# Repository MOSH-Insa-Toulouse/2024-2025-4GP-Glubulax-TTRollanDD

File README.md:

# 2024-2025 : Projet de capteur graphène low-tech – Sombret Yanis, Rolland Tristan

## SOMMAIRE

- [2024-2025 : Projet de capteur graphène low-tech – Sombret Yanis, Rolland Tristan](#2024-2025--projet-de-capteur-graphène-low-tech--sombret-yanis-rolland-tristan)
  - [SOMMAIRE](#sommaire)
  - [Présentation du projet](#présentation-du-projet)
  - [Livrables](#livrables)
  - [Matériel nécessaire](#matériel-nécessaire)
  - [Simulation électronique du capteur sous LTSpice](#simulation-électronique-du-capteur-sous-ltspice)
  - [Design du PCB sous KiCad et réalisation de la Shield](#design-du-pcb-sous-kicad-et-réalisation-de-la-shield)
  - [Code Arduino et applications](#code-arduino-et-applications)
  - [Test et résultats](#test-et-résultats)
  - [Datasheet](#datasheet)
  - [Conclusions et analyse critique du projet](#conclusions-et-analyse-critique-du-projet)
  - [Contacts](#contacts)

## Présentation du projet

&nbsp;&nbsp;&nbsp;&nbsp;&nbsp;&nbsp;Dans le cadre de l’UF «Du capteur au banc de test», nous avons eu pour projet de designer et produire un système de mesure de déformation d’une jauge de contrainte low-tech, un morceau de papier sur lequel est dessiné une piste au crayon à papier. Cette technologie bas coût de jauge de contrainte provient des travaux de Cheng-Wei Lin, Zhibo Zhao, Jaemyung Kim et Jiaxing Huang, chercheurs du département des sciences de l’ingénierie et des matériaux de l’université Northwestern à Evanston, USA. En effet, les traces de crayons laissées sur le papier jouent le rôle de fines couches de graphène conductrices. 

&nbsp;&nbsp;&nbsp;&nbsp;&nbsp;&nbsp;En fonction de la contrainte appliquée à notre jauge, l’écartement des particules de graphène se voit modifié, altérant les propriétés conductrices de notre couche de graphène. Grossièrement, effectuer une flexion sur notre capteur revient à écarter les agglomérats de graphène diminuant la conductivité, effectuer une compression revient à produire l’effet inverse en rapprochant les agglomérats de graphène. 

&nbsp;&nbsp;&nbsp;&nbsp;&nbsp;&nbsp;Par mesure de tension en sortie d’amplificateur, il est possible de remonter à la valeur de la résistance du capteur et la mettre en regard de la déformation. Enfin, la quantité de graphène dépend du type de crayon employé influant aussi la conductivité de la couche obtenue. 

&nbsp;&nbsp;&nbsp;&nbsp;&nbsp;&nbsp;Ainsi, en plus de l’intérêt pédagogique de ce projet de conception qui nous a permis d’intervenir sur toute la chaîne d’acquisition, nous avons eu l’occasion, et pour mission, de faire une étude qualitative du banc de test et déterminer ainsi si le capteur pouvait faire l’objet d’une commercialisation, et si oui, avec quel type de crayon à papier. 

&nbsp;&nbsp;&nbsp;&nbsp;&nbsp;&nbsp;Dans le cadre de la réalisation et de la caractérisation de ce dispositif de mesure low-tech, il nous a fallu suivre différentes étapes allant de la simulation électronique à la rédaction de sa datasheet en passant par l’impression de notre Shield PCB sur lequel nous avons fait nos soudures.

Dans ce README, nous faisons état de tout ce qui a été fait dans le cadre de ce projet.

## Livrables

Plusieurs livrables sont attendus :

- **Un Shield PCB connecté à une carte Arduino UNO** avec différents composants : un capteur graphite, un amplificateur transimpédance, un module Bluetooth, un écran OLED, un flexsensor commercial, un potentiomètre digital, un encodeur rotatoire ;
- **Le code Arduino lié** permettant de contrôler les différents composants intégrés et de faire fonctionner les différentes fonctionnalités de notre assemblage (mesures de contraintes, échanges Bluetooth et OLED, potentiomètre digital et boutons) ;
- **Une application Android** (sous MIT App Inventor) interfaçant le PCB et le code Arduino correspondant, aidant à la prise des mesures ;
- **La datasheet du capteur** reprenant toutes les caractéristiques notre capteur low-tech.

## Matériel nécessaire

Afin de mener notre projet à son aboutissement, nous avons eu besoin de :

*Pour le montage de l'amplificateur transimpédance : *

- Résistances fixes : 1 kΩ x1, 10 kΩ x1, 100 kΩ x2 ; une résistance variable (le potentiomètre digital), afin de pouvoir régler le gain de notre amplificateur ;
- Une résistance variable (Potentiomètre digital MCP41050 et son support), afin de pouvoir régler le gain de notre montage amplificateur ;
- Amplificateur opérationnel LTC1050 et son support ;
- Capacités : 100 nF x3, 1 μF x1.

*Pour le reste de notre Shield :*

- Arduino Uno et son câble d’alimentation, notre carte d’acquisition ;
- Résistance : une de 33kΩ similaire à la résistance au repos du flexsensor afin de réaliser un pont diviseur de tension ;
- Module Bluetooth HC05 ;
- Ecran OLED de dimension 128*64 ;
- Flexsensor ;
- Encodeur rotatoire ;
- Capteur graphite et 2 pinces crocodiles ;

## Simulation électronique du capteur sous LTSpice

&nbsp;&nbsp;&nbsp;&nbsp;&nbsp;&nbsp;Notre capteur passif en graphène possède une très grande résistance, de l’ordre du mégaohm. Ainsi, une fois alimenté par la carte Arduino en 5V à ces bornes, le courant est très faible. Or, il est notre signal d’intérêt pour remonter à la valeur de la résistance de notre capteur. Ainsi, il est nécessaire de mettre en place un amplificateur transimpédance afin d’amplifier le signal, le convertir en tension, et enfin de diminuer les bruits en entrés qui pourrait parasiter notre signal trop faible. Pour se faire, nous avons d’abord modélisé l’amplificateur sous LTspice afin d’optimiser au mieux sa conception pour notre application.

***Description du montage amplificateur transimpédance***

Nous avons testé ce [montage](https://github.com/MOSH-Insa-Toulouse/2024-2025-4GP-Glubulax-TTRollanDD/blob/5d5dbacb22e8d05c2202cd88c66fef8cc0433a9e/LTspice/Ampli_transimp%C3%A9dance/Ampli_transimp%C3%A9dance.asc) sur le logiciel LTspice :

Via ce montage, on a le rapport :

Vcc/Vadc=(Rcapteur+R1+R5)/(1+R3/R2)R1

On peut donc remonter à la valeur de la résistance du capteur :

Rcapteur=(1+R3/R2)R1*Vcc/Vadc-R1-R5

&nbsp;&nbsp;&nbsp;&nbsp;&nbsp;&nbsp;Aussi, nous remplacerons R2 sur notre PCB finale par un potentiomètre digital afin de pouvoir régler pendant nos mesures le gain du montage dans le cas de saturation par exemple.

&nbsp;&nbsp;&nbsp;&nbsp;&nbsp;&nbsp;Le choix de l’amplificateur opérationnel de notre circuit ici est crucial. Celui-ci doit être capable d'accepter en entrée un très faible courant et posséder un offset de tension très faible afin de ne pas fausser les valeurs de tension en sortie du montage. Contraintes vérifiées par simulation. Après plusieurs essaies guidés, le choix le plus pertinent était l’AOP LTC 1050.

&nbsp;&nbsp;&nbsp;&nbsp;&nbsp;&nbsp;Place maintenant à la réduction du bruit. Pour obtenir un signal le plus pur et ce, de manière efficace, nous avons dimensionné les 3 filtres de ce montage amplificateur transimpédance via nos simulations. Chaque filtre ayant un rôle bien précis : 

- à l'entrée, un filtre 1 passe-bas passif (R5,R1,C1) avec une fréquence de coupure de 16 Hz permettant de filtrer les bruits sur le signal en entrée fournis par nos capteurs. Donc tout type de perturbations en courant qu’il pourrait avoir lieu avant amplification, qui serait amplifié dans le cas contraire avec notre signal, le noyant.

- un deuxième filtre 2 passe-bas avec une fréquence de coupure de 1.6 Hz (R3,C4) couplé à l'AOP permettant de filtrer la composante du bruit à 50 Hz provenant du réseau électrique. Ici, la simulation nous a permis de fixer la valeur de C4. Une valeur trop élevée permet de diminuer grandement le bruit à 50 Hz mais diminue fortement le temps de réponse de notre circuit amplificateur. Ainsi, après simulation, fixer C4 à 1μF représente le meilleur compromis. 

- à la sortie de l'amplificateur, le filtre 3 (R6,C2) avec une fréquence de coupure de 1.6 kHz permettant de filtrer le bruit provenant du fonctionnement du LTC1050 (bruits des alimentation, de l'horloge, etc...).

&nbsp;&nbsp;&nbsp;&nbsp;&nbsp;&nbsp;Enfin, la résistance R5 en entrée, en plus de former avec la capacité C1 un filtre éliminant les bruits en tension, protège l'AOP contre les décharges électrostatiques et permet d’obtenir la conversion du signal en tension. La résistance R1 sert de résistance de shunt entre la source de courant et la masse.

***Résultats simulations***

&nbsp;&nbsp;&nbsp;&nbsp;&nbsp;&nbsp;Comme énoncé précédemment, la simulation nous a permis de vérifier la théorie et d’optimiser certains filtres afin d’obtenir les meilleurs rapports signal/temps de réponse. Voici les résultats des simulations.

&nbsp;&nbsp;&nbsp;&nbsp;&nbsp;&nbsp;On observe bien ci-dessus l’amplification du signal. L'Arduino pourra donc l'interpréter. De plus, on vérifie que plus C4 est élevée, meilleur le signal est mais plus le temps de réponse est long.

&nbsp;&nbsp;&nbsp;&nbsp;&nbsp;&nbsp;Ci-dessous les résultats de nos simulations à courant alternatifs afin de vérifier et optimiser le rôle de chacun des filtres. Le bruit est atténué d’environ 72dB à 50Hz. Le montage est performant.

## Design du PCB sous KiCad et réalisation de la Shield

***Modélisation sous KiCad***

&nbsp;&nbsp;&nbsp;&nbsp;&nbsp;&nbsp;Une fois les étapes de vérification faites, nous pouvions commencer le design et la conception de notre banc de test. Pour se faire nous avons utilisé le logiciel de modélisation KiCad 9.0, qui permet de modéliser tous les composants dont nous avions besoin sur une Shield de taille identique à la plaquette Arduino qui servira de carte d’acquisition. De là, nous pouvions modéliser nos différents composant et faire la connectique, étape très importante étant donné la petitesse de notre PCB en regard des composants qu’elle accueillerait. Afin de réaliser nos mesures avec le plus de pertinence et de confort, nous avons eu recourt à:

- un flexsensor commercial d’une résistance au repos de 33kΩ, afin de pouvoir comparer nos mesures avec celle des capteurs graphites.

- un module bluetooth HC-05 permettant d’envoyer les données mesurées sur notre téléphone via une application Android codé par nos soins sur MIT APP Inventor.

- un écran OLED permettant d’afficher un menu sur lequel nous pouvons régler la valeur de la résistance du potentiomètre digital ainsi qu’observer la valeur des résistances du flexsensor et des capteurs graphènes. 

&nbsp;&nbsp;&nbsp;&nbsp;&nbsp;&nbsp;Pour la modélisation, nous avons commencé par faire la schématique. Cette dernière permet de visualiser et de faire tous les branchements nécessaires au bon fonctionnement de notre banc de test. Fi de fils de connections, c’est le fonctionnement qui importe. Nous avons dû créer nous même certains symboles non présents dans les bibliothèques déjà existantes. Notre seule contrainte ici était de connecter les bons éléments aux pins d’intérêts de l’arduino. En effet, certain composant nécessitait d’être connecté à des pins PWM de l’arduino pour cadencer l’information via une clock. C’est le cas pour le module HC-05 en écriture au moins et l’encodeur digital. Voici donc notre proposition :

&nbsp;&nbsp;&nbsp;&nbsp;&nbsp;&nbsp;Par la suite, nous avons créé les empreintes de chacun des composants afin de modéliser notre Shield PCB. C’est à cette étape que nous prenions en compte les pistes de cuivres et l’agencement des composants pour que tout rentre sur l’espace imposé et que tout soit connecté selon la schématique que nous avions produit précédemment. Aussi, il nous a fallu prêter grande attention aux masses flottantes et aux piscines. Les masses flottantes pouvaient générer des disfonctionnements sur notre banc. Quant aux piscines, de larges zones sans cuivre, elles posaient un problème de gaspillage, les pistes après modélisation se faisant par enlèvement de matière.  

&nbsp;&nbsp;&nbsp;&nbsp;&nbsp;&nbsp;Il nous a également fallu prendre en compte les dimensions de chaque composant pour éviter qu’ils ne se chevauchent au moment de la réalisation :

&nbsp;&nbsp;&nbsp;&nbsp;&nbsp;&nbsp;Les fichiers KiCad sont disponibles dans le dossier [KiCad arduino uno](https://github.com/MOSH-Insa-Toulouse/2024-2025-4GP-Glubulax-TTRollanDD/tree/5d5dbacb22e8d05c2202cd88c66fef8cc0433a9e/Kicad%20arduino%20uno/Capteur_graphite).

***Réalisation de la Shield***

&nbsp;&nbsp;&nbsp;&nbsp;&nbsp;&nbsp;Modélisation terminée, nous avons pu passer à la réalisation physique de notre Shield. Voici les étapes de fabrication réalisées :

Étape 0 (importante !) : vérification du PCB sous KiCad ;
Étape 1 : édition du masque de gravure de notre PCB sous KiCad ;
Étape 2 : insolation UV d'une plaquette d'époxy recouverte d'une couche de cuivre et de résine photosensible ;
Étape 3 : immersion de la plaquette dans un révélateur afin d'éliminer la résine non-insolée ;
Étape 4 : immersion de la plaquette dans du perchlorure de fer pour graver les pistes ;
Étape 5 : nettoyage de la plaquette avec de l'acétone pour retirer la résine restante.

&nbsp;&nbsp;&nbsp;&nbsp;&nbsp;&nbsp;Toutes ces étapes de fabrication ont été réalisées par Cathy Crouzet. Nous avons ensuite pu réaliser le perçage de notre plaquette et y souder nos divers composants selon le schéma du PCB obtenu sur KiCad.

Voici le résultat après soudure de notre PCB :

## Code Arduino et applications

***Arduino***

&nbsp;&nbsp;&nbsp;&nbsp;&nbsp;&nbsp;Une fois le Shield PCB réalisé, nous avons d’abord réalisé le code Arduino qui nous permettrait de coordonner tous nos composants et procéder nos mesures.

&nbsp;&nbsp;&nbsp;&nbsp;&nbsp;&nbsp;Nous avons décidé de donner une importance particulière à l’écran OLED, notre but étant de configurer un petit menu pour y sélectionner les valeurs de résistance du potentiomètre et pour y voir les valeurs de résistance mesurées. Le fonctionnement de l’affichage OLED se fait en parallèle de la mesure, à chaque tour de boucle, que l’on soit ou non sur la partie du menu nous permettant de voir la mesure, un signal est récupéré. 

&nbsp;&nbsp;&nbsp;&nbsp;&nbsp;&nbsp;Le deuxième élément qui nous a demandé beaucoup d’attention était le module Bluetooth. Nous avons opté pour un fonctionnement simple lié au menu d’affichage de l’écran OLED. Si la mesure se fait de manière constante, l’envoie de données lui ne l’est pas. Si nous nous trouvons sur la page du menu de configuration de la valeur du potentiomètre, l’information envoyée est un entier compris entre 1 et 8 codé sur 8 bits. Si nous nous trouvons sur la page du menu affichant les valeurs de résistance, l’information envoyée est un entier compris entre 0 et 255 codé sur 8 bits également.

&nbsp;&nbsp;&nbsp;&nbsp;&nbsp;&nbsp;Ici n’est qu’un bref résumé du fonctionnement de notre code. Notre [code](https://github.com/MOSH-Insa-Toulouse/2024-2025-4GP-Glubulax-TTRollanDD/blob/5d5dbacb22e8d05c2202cd88c66fef8cc0433a9e/Kicad%20arduino%20uno/partie_software/code_arduino/code_arduino.ino) complet et commenté se trouve sur le GitHub.

***Application Android***

&nbsp;&nbsp;&nbsp;&nbsp;&nbsp;&nbsp;Enfin, avant de pouvoir commencer à mesurer, nous avons procédé à la création d’une application Android sur MIT APP Inventor afin de mieux visualiser les données. Le fonctionnement de notre code block est directement lié à notre code Arduino du HC-05. En fonction de la donnée reçue, nous complétons le champ « valeur résistance SPI » ou « valeur résistance mesurée ».

&nbsp;&nbsp;&nbsp;&nbsp;&nbsp;&nbsp;Nous avons fait face à de nombreux problème lors de sa réalisation, le plus gros étant le cadencement des données. En effet, notre HC-05 envoyait pléthore de données et saturait le buffer de réception. Ainsi nous pouvions arrêter les mesures à un temps T et n’arrêter d’en afficher les variations sur l’application qu’une à deux minutes plus tard. Nous avons résolu ce problème en réglant la clock de l’application pour la caler sur le bauderate de l’Arduino. Une fois fait, nous avons tenté de faire un graphique en temps réel pour visualiser les variations mais celui-ci n’a pas abouti, les variations étant trop rapides et trop grandes. 

Idem, l’[application](https://github.com/MOSH-Insa-Toulouse/2024-2025-4GP-Glubulax-TTRollanDD/blob/5d5dbacb22e8d05c2202cd88c66fef8cc0433a9e/Kicad%20arduino%20uno/Appli_Apk/Capteur.apk) est disponible sur le GitHub.

## Test et résultats

&nbsp;&nbsp;&nbsp;&nbsp;&nbsp;&nbsp;Afin de réaliser nos tests et mesures avec la plus grande précision et confort possible, nous voulions nous assurer des contraintes que nous appliquions sur nos jauges. Nos jauges car nous avons confectionné plusieurs jauges de contrainte avec des types de crayon différents dans l’optique de pouvoir les comparer les unes aux autres et déterminer laquelle serait la plus performante ou la plus conductrice. Celles-ci sont toutes de dimensions fixes avec une épaisseur de papier fixe.

Or, la déformation ε dans notre cas se calcule comme :  

&nbsp;&nbsp;&nbsp;&nbsp;&nbsp;&nbsp;ε=e/(2*R0)

Où e est l’épaisseur de nos jauges, et R0 le rayon de courbure. Ainsi, pour pouvoir appliquer la même contrainte et donc observer la même déformation sur toutes nos jauges de contrainte, nous avons modélisé et fabriqué le petit outil de test ci-dessus.

Il dispose de 6 encoches dans lesquelles nous pouvons glisser nos jauges en papiers. Les 6 encoches sont de dimensions fixes et donc, applique une contrainte similaire sur chacune des jauges à tester. 

&nbsp;&nbsp;&nbsp;&nbsp;&nbsp;&nbsp;De fait, avec des conditions de mesure similaire, nous avons pu comparer les différents capteurs les uns aux autres et produire le tableau de [résultats](https://github.com/MOSH-Insa-Toulouse/2024-2025-4GP-Glubulax-TTRollanDD/blob/5d5dbacb22e8d05c2202cd88c66fef8cc0433a9e/R%C3%A9sultats/Mesures.xlsx) disponible sur notre GitHub. Cependant, comme développé en conclusion nous avons rencontré quelques soucis durant nos mesures amenant à des quelques aberrations. Par exemple ci-dessous on peut voir sur le graphique avec la valeur du potentiomètre fixé à 12500 Ω que le ∆R/R est plus marqué pour le 2B et le B que pour le 3B. Or, le 3B est censé être plus gras que le B et le 2B, il devrait donc avec des ∆R/R plus élevé pour une même déformation.

Aussi, ci-dessous nous pouvons voir les valeurs de résistances en fonction de la déformation pour différents crayons, potentiomètre fixé à 12500 Ω. Sur ce graphique, on constate que la résistance du crayon HB ne correspond pas à la théorie, moins gras, sa résistance devrait être grandement supérieur aux crayons de type B et plus.

On peut expliquer cette constatation par le fait que chaque jauge a été dessiné en appuyant la mine des crayons de manière plus ou moins forte sur le papier, déposant des quantités de graphènes différentes. Ainsi, ici, on peut supposer que le capteur HB a été dessiné avec violence, ce qui a fortement diminué sa résistance dû à la forte concentration de graphène malgré le crayon peu gras qu’est le HB.

## Datasheet

La datasheet de notre capteur est disponible [ici](https://github.com/MOSH-Insa-Toulouse/2024-2025-4GP-Glubulax-TTRollanDD/blob/5d5dbacb22e8d05c2202cd88c66fef8cc0433a9e/Datasheet.pdf).

## Conclusions et analyse critique du projet

&nbsp;&nbsp;&nbsp;&nbsp;&nbsp;&nbsp;Ce projet a été très enrichissant d’un point de vue pédagogique. Ce fut l’occasion pour nous développer plusieurs compétences de savoir-faire. Des compétences de savoir-faire car via ce projet nous avons pu intervenir et manipuler à tous les niveaux de la chaîne d’acquisition, faisant le lien entre des phénomènes physiques et le monde du numérique beaucoup plus pratique pour l’analyse. A ça, nous avons pu développer des compétences en électroniques très importantes, notamment au niveau de la réduction de bruit pour ne garder que le signal d’intérêt, parfois très faible, mais garder un temps de réponse raisonnable. Enfin, à travers ce projet nous avons obtenu une première approche de confection de datasheet, très importante bien que peu attirante, pour faciliter la lecture de nos travaux.

&nbsp;&nbsp;&nbsp;&nbsp;&nbsp;&nbsp;En ce qui concerne les capteurs graphites fabriqués, ils sont fonctionnels et les tests nous permettent de dégager des tendances cohérentes avec la physique. Cependant, nos capteurs présentaient des valeurs relativement variables. D’un jour à l’autre nous n’obtenions pas tout à fait les mêmes résultats pour une même jauge, bien que nous ayons fixé les contraintes appliquées via notre outil de mesure. De plus, notre outil du fait des encoches, gratte la fine couche de graphène et en enlève, altérant les propriétés des capteurs. Aussi, on observait des oscillations constantes dans nos mesures mettant en évidence, malgré nos filtres, un bruit externe venant les perturber. A ça nous aurions pu, par exemple, pour améliorer notre dispositif blinder les câbles, mais aussi notre Shield. De fait, il est nécessaire de prendre du recul sur les résultats que nous proposons.

## Contacts

Pour toute information complémentaire, vous pouvez nous contacter à ces adresses mails :

- Sombret Yanis : <sombret@insa-toulouse.fr>
- Rolland Tristan : <rollan@insa-toulouse.fr>

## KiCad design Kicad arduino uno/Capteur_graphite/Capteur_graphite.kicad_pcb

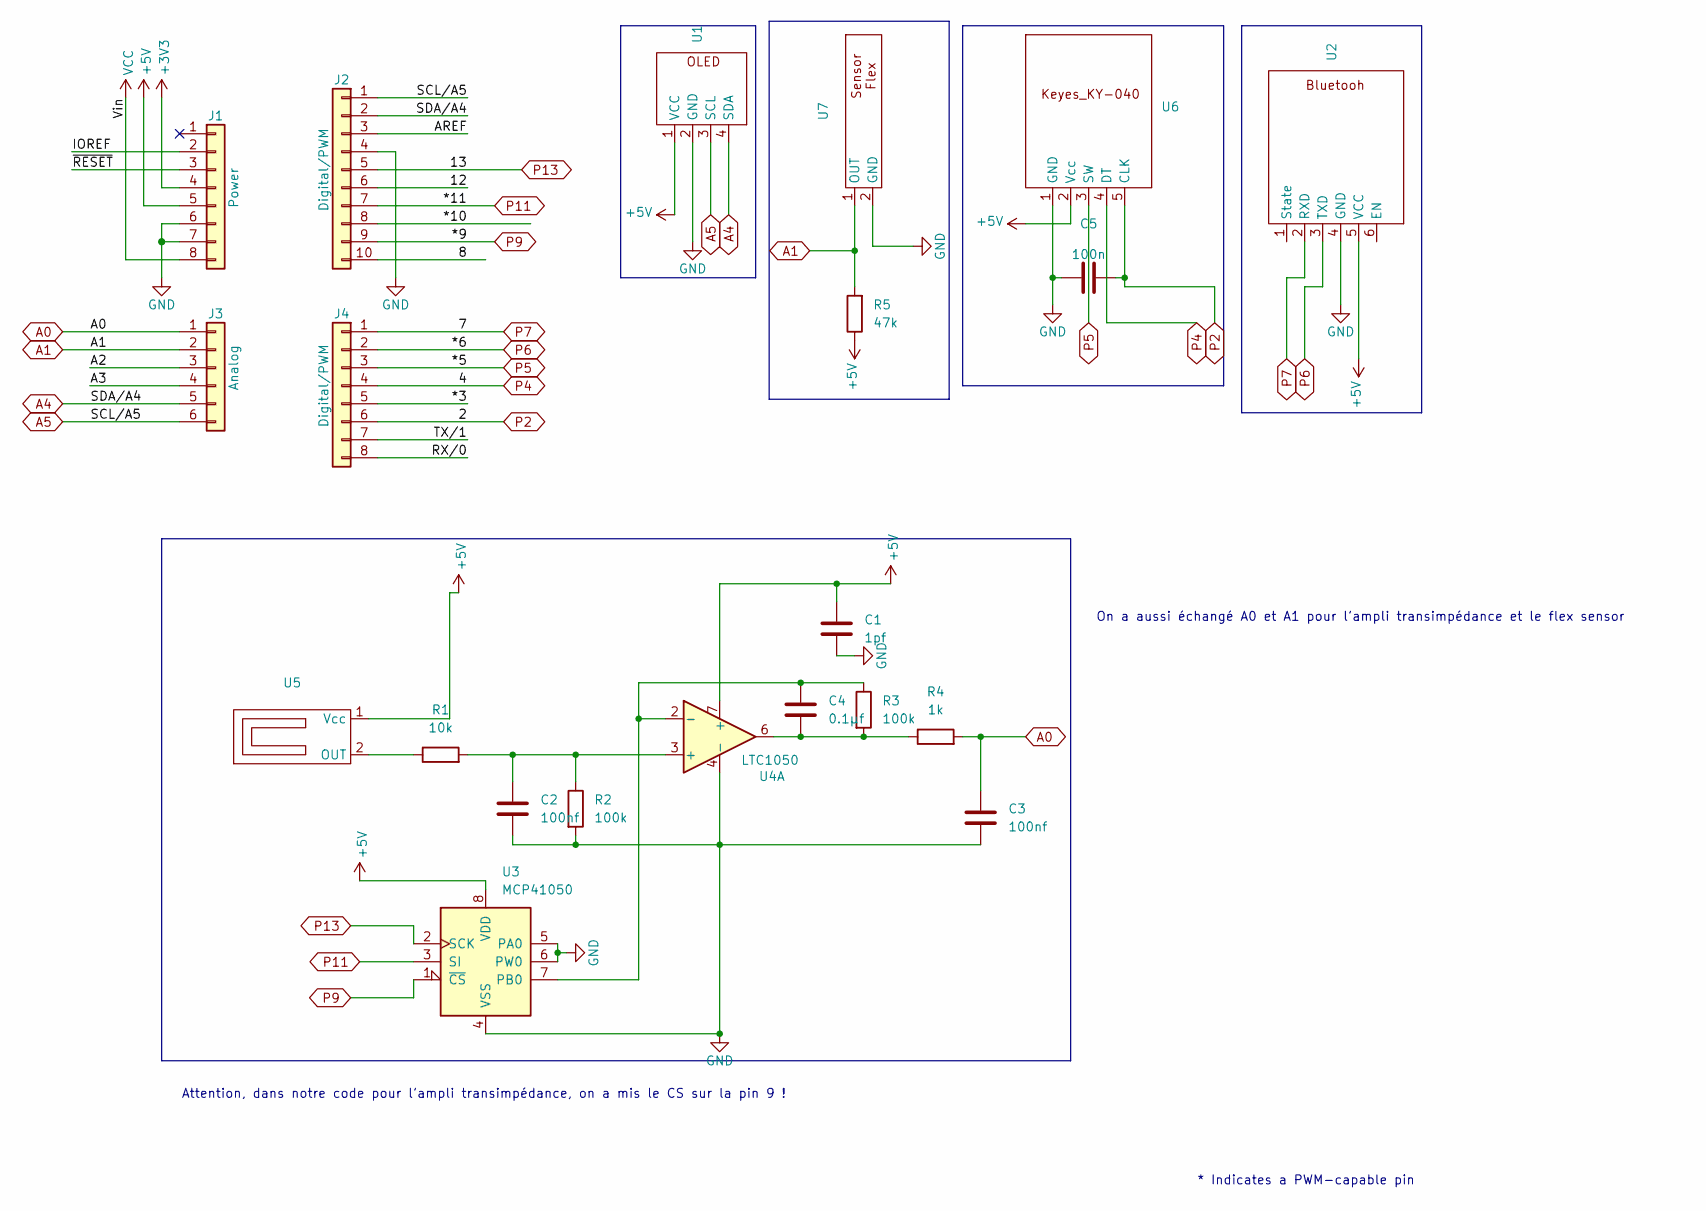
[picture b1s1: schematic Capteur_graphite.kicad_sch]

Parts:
C1: 1pf; C_Disc_D7.0mm_W2.5mm_P5.00mm
C2, C3: 100nf; C_Disc_D7.0mm_W2.5mm_P5.00mm
C4: 0.1µf; C_Disc_D7.0mm_W2.5mm_P5.00mm
C5: 100n; C_Disc_D7.0mm_W2.5mm_P5.00mm
J1: Power; PinSocket_1x08_P2.54mm_Vertical
J2: Digital/PWM; PinSocket_1x10_P2.54mm_Vertical
J3: Analog; PinSocket_1x06_P2.54mm_Vertical
J4: Digital/PWM; PinSocket_1x08_P2.54mm_Vertical
R1: 10k; R_Axial_DIN0204_L3.6mm_D1.6mm_P7.62mm_Horizontal
R2, R3: 100k; R_Axial_DIN0204_L3.6mm_D1.6mm_P7.62mm_Horizontal
R4: 1k; R_Axial_DIN0204_L3.6mm_D1.6mm_P7.62mm_Horizontal
R5: 47k; R_Axial_DIN0204_L3.6mm_D1.6mm_P7.62mm_Horizontal
U1: OLED
U2: BLUETOOTH
U3: MCP41050
U4: LTC1050
U5: Capteur
U6: Keyes KY_040
U7: Flex

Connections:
+3V3: J1.4
+5V: C1.1, J1.5, R5.1, U1.1 (VCC), U2.5 (VCC), U3.8 (VDD), U4.7 (+), U5.1 (Vcc), U6.2 (Vcc)
/8: J2.10
/12: J2.6
/*3: J4.5
/*10: J2.8
/A2: J3.3
/A3: J3.4
/AREF: J2.3
/IOREF: J1.2
/RX/0: J4.8
/TX/1: J4.7
/~RESET: J1.3
A0: C3.2, J3.1, R4.2
A1: J3.2, R5.2, U7.1 (OUT)
A4: J2.2, J3.5, U1.4 (SDA)
A5: J2.1, J3.6, U1.3 (SCL)
GND: C1.2, C2.1, C3.1, C5.1, J1.6, J1.7, J2.4, R2.2, U1.2 (GND), U2.4 (GND), U3.4 (VSS), U3.5 (PA0), U3.6 (PW0), U4.4 (-), U6.1 (GND), U7.2 (GND)
unnamed: C2.2, R1.2, R2.1, U4.3 (+)
unnamed: C4.1, R3.2, R4.1, U4.6
unnamed: C4.2, R3.1, U3.7 (PB0), U4.2 (-)
unnamed: R1.1, U5.2 (OUT)
P2: C5.2, J4.6, U6.5 (CLK)
P4: J4.4, U6.4 (DT)
P5: J4.3, U6.3 (SW)
P6: J4.2, U2.3 (TXD)
P7: J4.1, U2.2 (RXD)
P9: J2.9, U3.1 (~CS)
P11: J2.7, U3.3 (SI)
P13: J2.5, U3.2 (SCK)
VCC: J1.8

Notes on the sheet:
Attention, dans notre code pour l'ampli transimpédance, on a mis le CS sur la pin 9 !
On a aussi échangé A0 et A1 pour l'ampli transimpédance et le flex sensor
* Indicates a PWM-capable pin

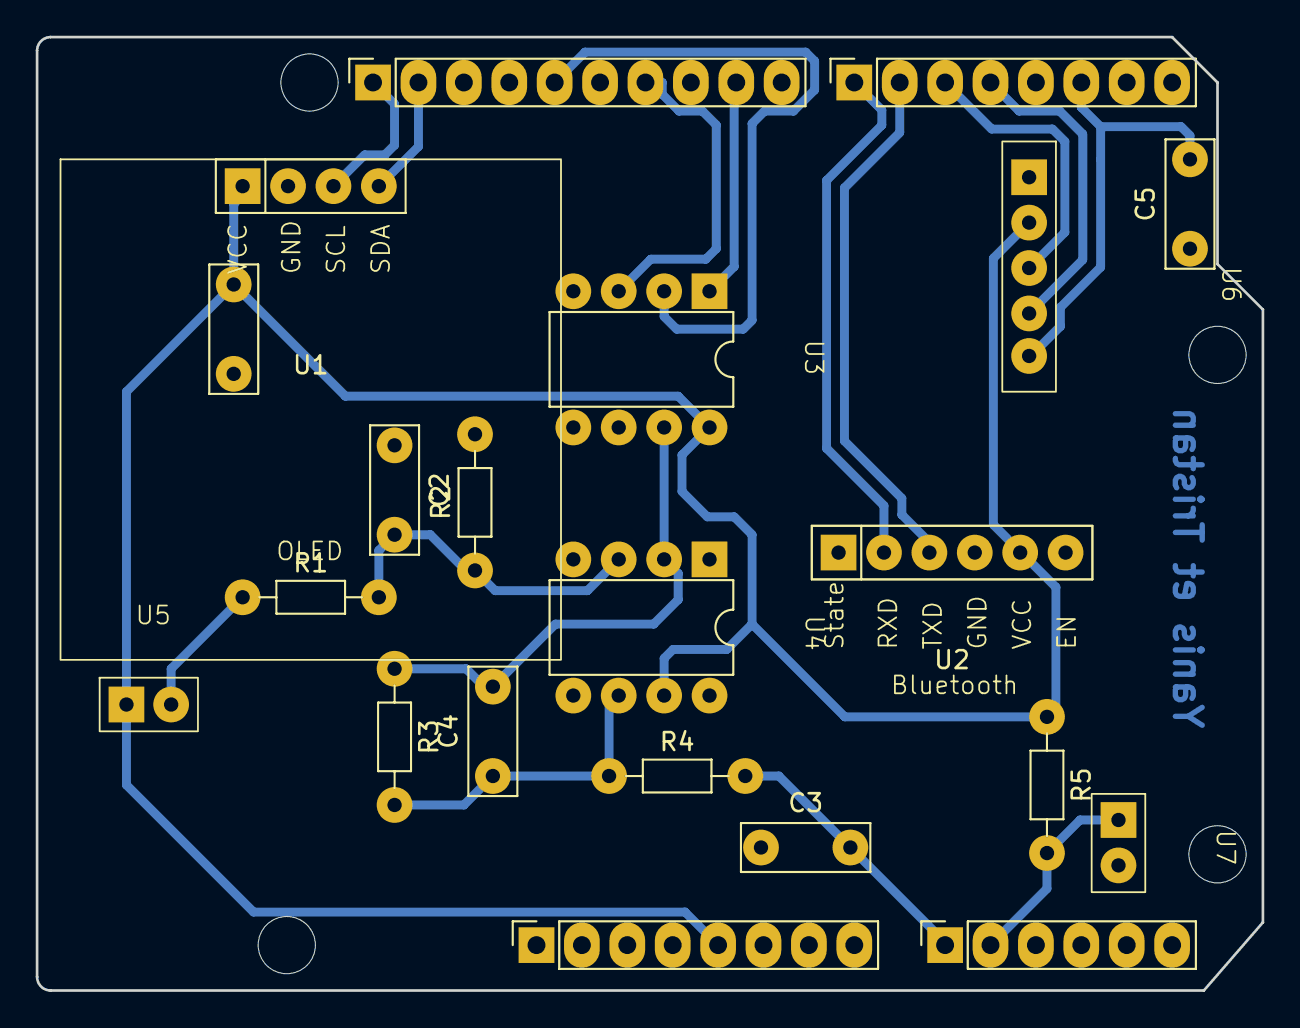
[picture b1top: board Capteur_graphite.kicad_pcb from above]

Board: 2 copper layers, 68.6 x 53.3 mm, 25 parts (0 on the bottom side), 18 nets.

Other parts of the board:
MH1, MH2, MH3, MH4: MountingHole_3.2mm

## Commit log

2025-02-19 Ajout de la toDo liste
2025-02-19 je change la ligne 7
2025-03-13 Test
2025-03-13 ajout Ltspice + tp_Mosh + Kicad
2025-03-13 erreur d'orthographe
2025-03-13 masse flottante à refaire
2025-03-18 Save_avec_via
2025-03-18 Save_sans_via_mais_avec_modif_pin
2025-03-18 sans_via_mais_bonne_modif_pin_(SCK_sur_la_13)
2025-03-19 pcb_verifiée_et_pin_size_modifiée
2025-03-19 ajout_dossier_gerber_et_fichier_impression
2025-03-19 pcb_verifiée_prêt_à_percer
2025-03-19 soucis_drill_invisible_rectifié
2025-03-28 soft_ware_beginning
2025-03-28 Software_bidouille
2025-04-02 Tout_marche_manque_le_bluetooth
2025-04-02 Bleutooth_ajouté_suis_heureux
2025-04-11 Ajout_results_HB
2025-04-11 Ajout_appli
2025-04-12 Résultats_complets
2025-04-23 Add photos
2025-04-23 Add README
2025-04-23 test2
2025-04-23 test3
2025-04-23 Add README sans datasheet
2025-04-23 Add Datasheet
2025-04-23 Add the good ones
2025-04-23 Add photos and results
2025-04-23 Add results
2025-04-23 FINITO
2025-04-29 Modif mesure
2025-05-23 Modif filtre R5
